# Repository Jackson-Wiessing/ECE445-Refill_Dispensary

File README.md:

# ECE445-Refill_Dispensary

**Welcome to our refill dispensary repo!**

**Introduction:** 

Plastic waste is a massive issue world-wide, particularly as it pertains to the packaging of food and other household goods. The United States Environmental Protection Agency estimates that in 2018, 14 million tons of plastic was consumed for packaging in the USA with about seventy percent of that ending up in landfills[1]. Plastic waste is detrimental to the environment as it doesn’t decompose naturally on human time scales. End-user plastic waste is often unnecessary as consumers own containers capable of being reused. 

We built a vending machine that dispenses precise quantities of goods (between 10 g and 5 kg) into reusable containers. The goal of the machine is to get users to keep bringing the same container back. In addition to plastic waste, our machine tackles the issue of waste in general as users are no longer forced to get quantities larger than desired. 

**High-level requirements:**
1. The user is able to choose an item and quantity to get dispensed via buttons and rotary potentiometers. Before placing the order, the user will have some indication of the amount ordered within a tolerance of 10 grams for weights between .1 kg and 2kg.
2. The machine dispenses two different types of low-viscosity liquids and is able to perform 2 orders in succession. 
3. The machine can deliver another order properly after 1 of the liquids is switched out or refilled. 

**Block Diagram:**

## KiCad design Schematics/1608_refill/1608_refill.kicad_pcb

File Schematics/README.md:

The easiest way to view our schematic and PCB layout is to download KiCad from https://www.kicad.org/download/. 
Once KiCad is downloaded, you'll need to clone this repo on your local machine.

To see the schematic open 1608_refill.kicad_sch.   

To see the PCB layout open 1608_refill.kicad_pcb.

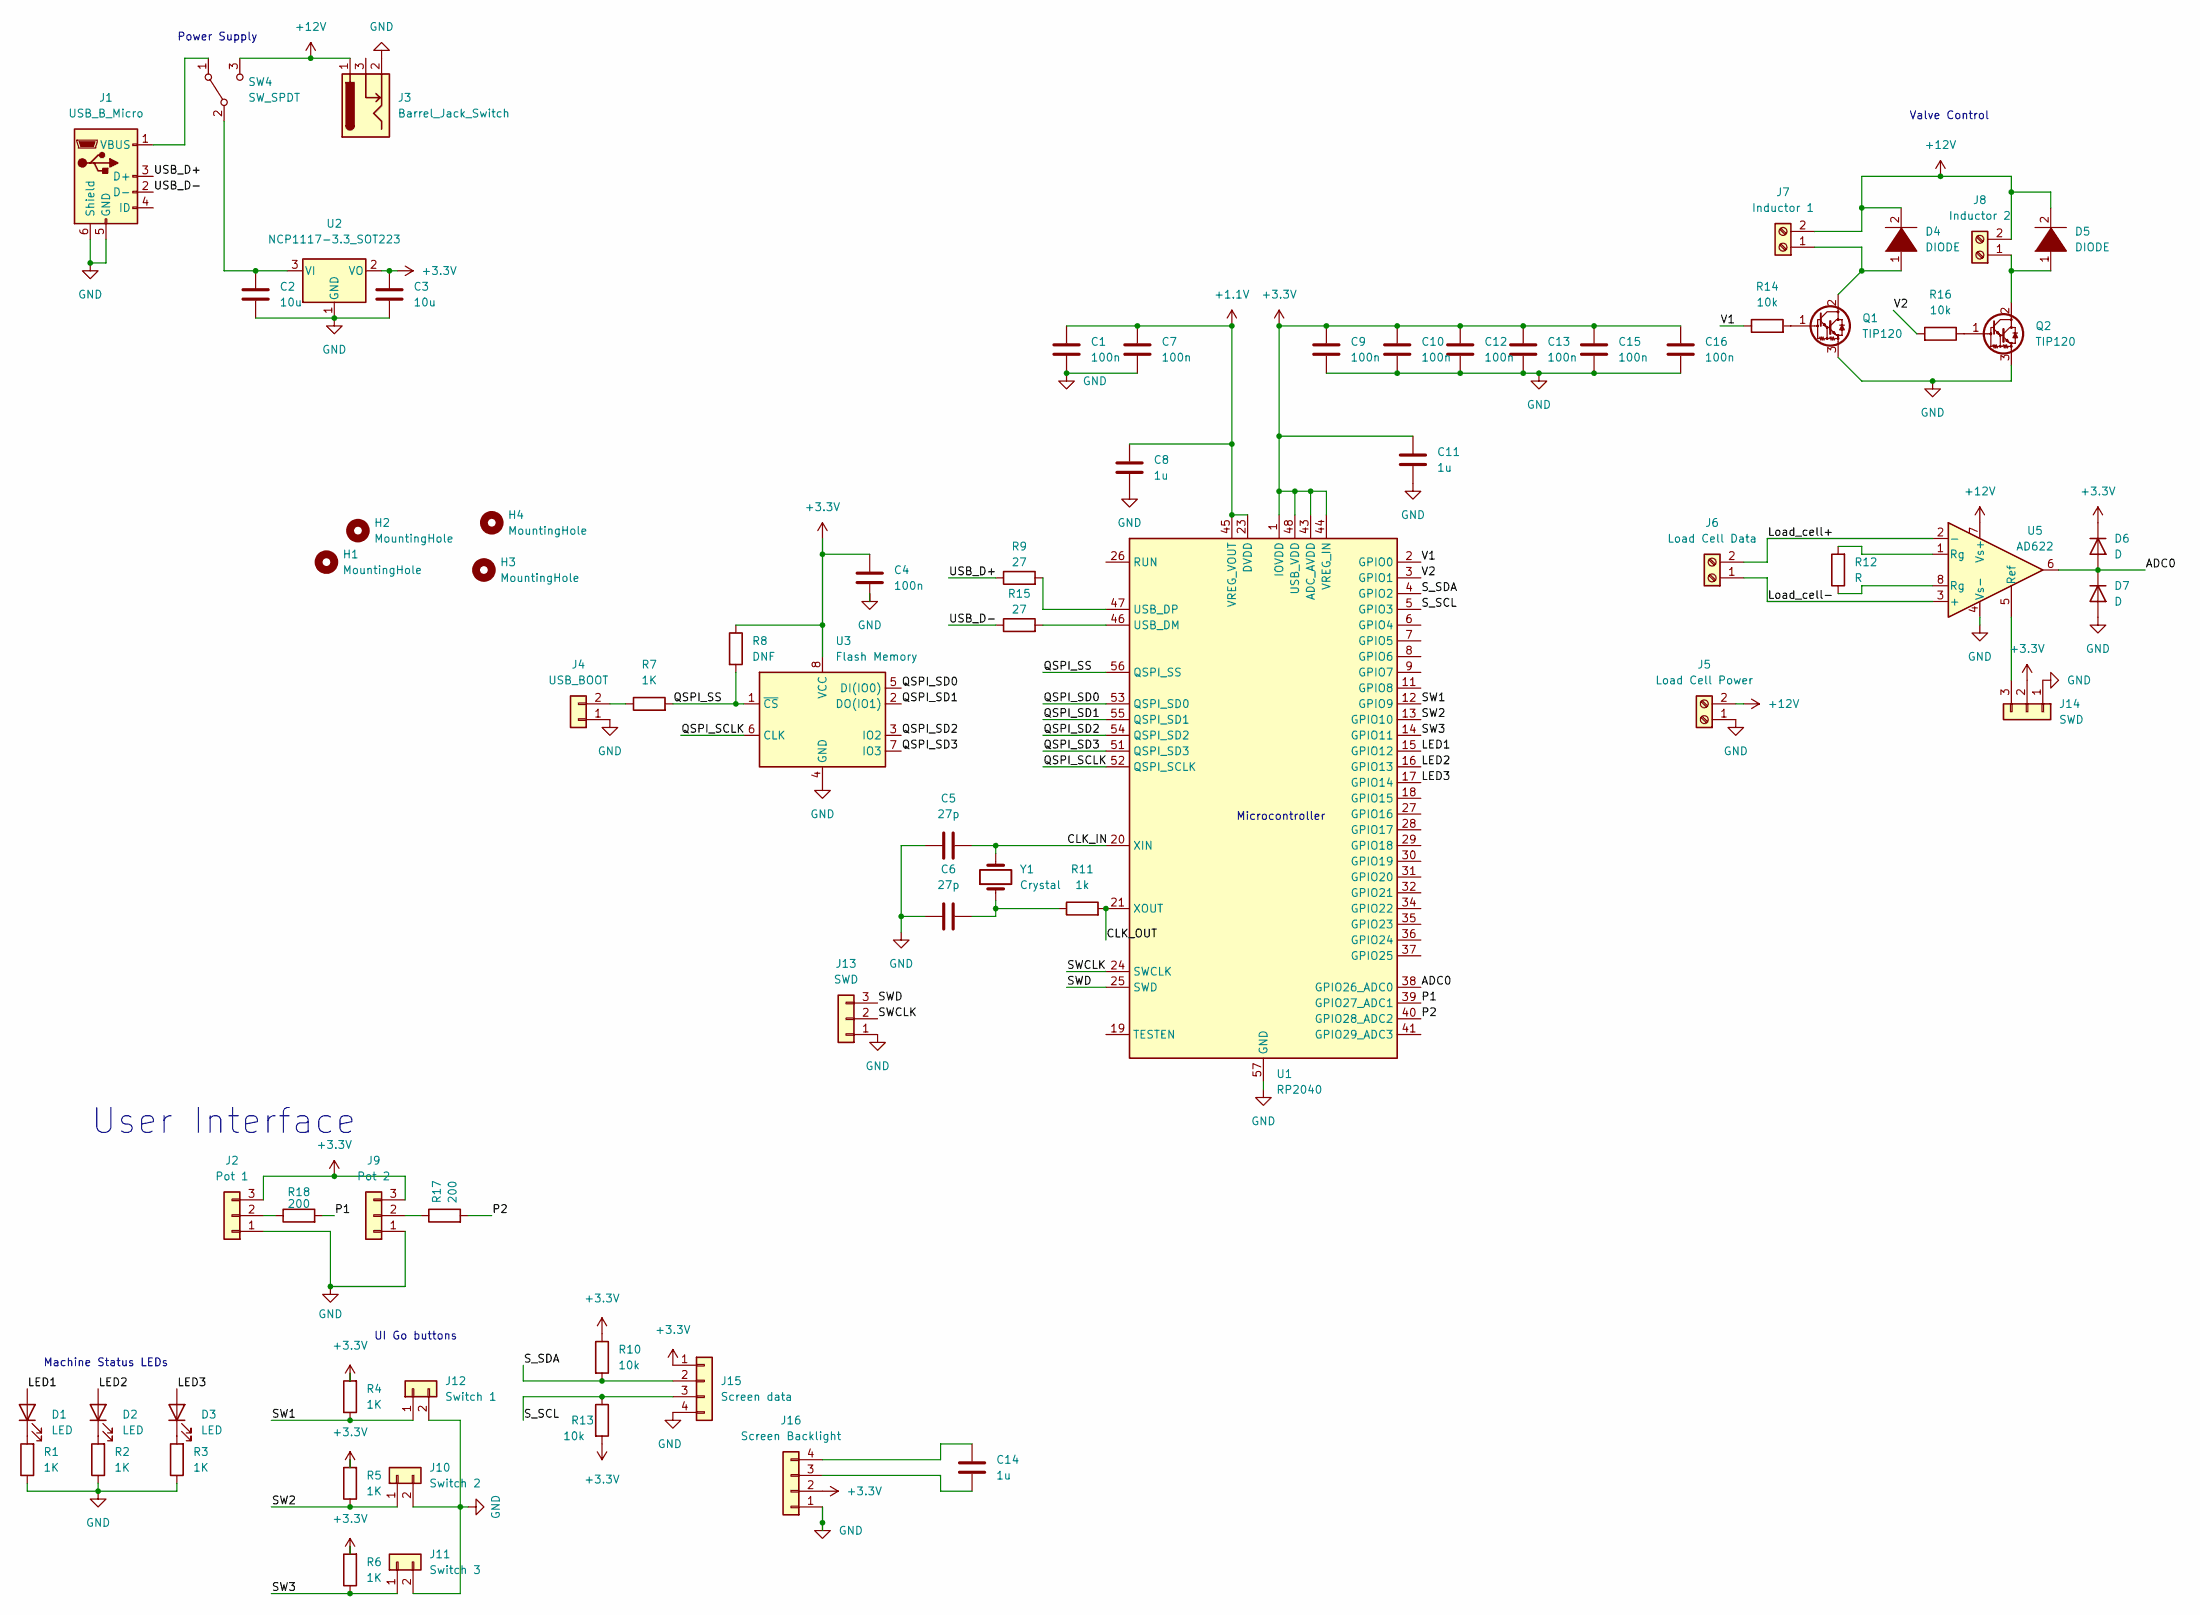
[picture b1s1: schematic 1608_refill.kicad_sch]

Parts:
C1, C4, C7, C9, C10, C12, C13, C15, C16: 100n; C_0603_1608Metric_Pad1.08x0.95mm_HandSolder
C2, C3: 10u; C_1210_3225Metric
C5, C6: 27p; C_0805_2012Metric
C8, C11, C14: 1u; C_0603_1608Metric_Pad1.08x0.95mm_HandSolder
D1, D2, D3: LED; LED_D3.0mm
D4, D5: DIODE; D_5W_P5.08mm_Vertical_AnodeUp
D6, D7: D; D_5W_P5.08mm_Vertical_AnodeUp
H1, H2, H3, H4: MountingHole; MountingHole_2.1mm
J1: USB_B_Micro; USB_Micro-AB_Molex_47590-0001
J2: Pot 1; JST_XH_B3B-XH-AM_1x03_P2.50mm_Vertical
J3: Barrel_Jack_Switch; BarrelJack_GCT_DCJ200-10-A_Horizontal
J4: USB_BOOT; JWT_A3963_1x02_P3.96mm_Vertical
J5: Load Cell Power; TerminalBlock_Altech_AK300-2_P5.00mm
J6: Load Cell Data; TerminalBlock_Altech_AK300-2_P5.00mm
J7: Inductor 1; TerminalBlock_Altech_AK300-2_P5.00mm
J8: Inductor 2; TerminalBlock_Altech_AK300-2_P5.00mm
J9: Pot 2; JST_XH_B3B-XH-AM_1x03_P2.50mm_Vertical
J10: Switch 2; JST_XH_B2B-XH-AM_1x02_P2.50mm_Vertical
J11: Switch 3; JST_XH_B2B-XH-AM_1x02_P2.50mm_Vertical
J12: Switch 1; JST_XH_B2B-XH-AM_1x02_P2.50mm_Vertical
J13, J14: SWD; JST_XH_B3B-XH-AM_1x03_P2.50mm_Vertical
J15: Screen data; JST_XH_B4B-XH-AM_1x04_P2.50mm_Vertical
J16: Screen Backlight; JST_XH_B4B-XH-AM_1x04_P2.50mm_Vertical
Q1, Q2: TIP120; TO-220-3_Vertical
R1, R2, R3, R4, R5, R6, R7: 1K; R_0603_1608Metric_Pad0.98x0.95mm_HandSolder
R8: DNF; R_0603_1608Metric_Pad0.98x0.95mm_HandSolder
R9, R15: 27; R_0805_2012Metric
R10, R13, R14, R16: 10k; R_0603_1608Metric_Pad0.98x0.95mm_HandSolder
R11: 1k; R_0603_1608Metric_Pad0.98x0.95mm_HandSolder
R12: R; R_Axial_DIN0204_L3.6mm_D1.6mm_P7.62mm_Horizontal
R17, R18: 200; R_0603_1608Metric_Pad0.98x0.95mm_HandSolder
SW4: SW_SPDT; SW_SPDT_CK-JS102011SAQN
U1: RP2040; QFN-56-1EP_7x7mm_P0.4mm_EP3.2x3.2mm
U2: NCP1117-3.3_SOT223; SOT-223-3_TabPin2
U3: Flash Memory; SOIC-8_5.23x5.23mm_P1.27mm
U5: AD622
Y1: Crystal; ABLS12MHZ

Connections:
+1V1: C1.1, C7.1, C8.1, U1.23 (DVDD), U1.45 (VREG_VOUT), U1.50 (DVDD)
+3.3V: C3.1, C4.1, C9.1, C10.1, C11.1, C12.1, C13.1, C15.1, C16.1, D6.1 (K), J2.3, J9.3, J14.2, J15.1, J16.2, R4.2, R5.2, R6.2, R8.1, R10.1, R13.2, U1.1 (IOVDD), U1.10 (IOVDD), U1.22 (IOVDD), U1.33 (IOVDD), U1.42 (IOVDD), U1.43 (ADC_AVDD), U1.44 (VREG_IN), U1.48 (USB_VDD), U1.49 (IOVDD), U2.2 (VO), U3.8 (VCC)
+12V: D4.2 (A), D5.2 (A), J3.1, J5.2, J7.2, J8.2, SW4.3 (C), U5.7 (Vs+)
/ADC0: D6.2 (A), D7.1 (K), U1.38 (GPIO26_ADC0), U5.6
/CLK_IN: C5.2, U1.20 (XIN), Y1.2
/CLK_OUT: R11.2, U1.21 (XOUT)
/LED1: D1.2 (A), U1.15 (GPIO12)
/LED2: D2.2 (A), U1.16 (GPIO13)
/LED3: D3.2 (A), U1.17 (GPIO14)
/Load_cell+: J6.2, U5.2 (-)
/Load_cell-: J6.1, U5.3 (+)
/P1: R18.2, U1.39 (GPIO27_ADC1)
/P2: R17.2, U1.40 (GPIO28_ADC2)
/QSPI_SCLK: U1.52 (QSPI_SCLK), U3.6 (CLK)
/QSPI_SD0: U1.53 (QSPI_SD0), U3.5 (DI(IO0))
/QSPI_SD1: U1.55 (QSPI_SD1), U3.2 (DO(IO1))
/QSPI_SD2: U1.54 (QSPI_SD2), U3.3 (IO2)
/QSPI_SD3: U1.51 (QSPI_SD3), U3.7 (IO3)
/QSPI_SS: R7.2, R8.2, U1.56 (QSPI_SS), U3.1 (~CS)
/SW1: J12.1, R4.1, U1.12 (GPIO9)
/SW2: J10.1, R5.1, U1.13 (GPIO10)
/SW3: J11.1, R6.1, U1.14 (GPIO11)
/SWCLK: J13.2, U1.24 (SWCLK)
/SWD: J13.3, U1.25 (SWD)
/S_SCL: J15.3, R13.1, U1.5 (GPIO3)
/S_SDA: J15.2, R10.2, U1.4 (GPIO2)
/USB_D+: J1.3 (D+), R9.1
/USB_D-: J1.2 (D-), R15.1
/V1: R14.1, U1.2 (GPIO0)
/V2: R16.2, U1.3 (GPIO1)
GND: C1.2, C2.2, C3.2, C4.2, C5.1, C6.1, C7.2, C8.2, C9.2, C10.2, C11.2, C12.2, C13.2, C15.2, C16.2, D7.2 (A), J1.5 (GND), J1.6 (Shield), J2.1, J3.2, J4.1, J5.1, J9.1, J10.2, J11.2, J12.2, J13.1, J14.1, J15.4, J16.1, Q1.3 (E), Q2.3 (E), R1.1, R2.1, R3.1, U1.57 (GND), U2.1 (GND), U3.4 (GND), U5.4 (Vs-)
unnamed: C2.1, SW4.2 (B), U2.3 (VI)
unnamed: C6.2, R11.1, Y1.1
unnamed: C14.1, J16.4
unnamed: C14.2, J16.3
unnamed: D1.1 (K), R1.2
unnamed: D2.1 (K), R2.2
unnamed: D3.1 (K), R3.2
unnamed: D4.1 (K), J7.1, Q1.2 (C)
unnamed: D5.1 (K), J8.1, Q2.2 (C)
unnamed: J1.1 (VBUS), SW4.1 (A)
unnamed: J2.2, R18.1
unnamed: J4.2, R7.1
unnamed: J9.2, R17.1
unnamed: J14.3, U5.5 (Ref)
unnamed: Q1.1 (B), R14.2
unnamed: Q2.1 (B), R16.1
unnamed: R9.2, U1.47 (USB_DP)
unnamed: R12.1, U5.8 (Rg)
unnamed: R12.2, U5.1 (Rg)
unnamed: R15.2, U1.46 (USB_DM)

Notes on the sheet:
Machine Status LEDs
Microcontroller
Power Supply
Valve Control
User Interface
UI Go buttons

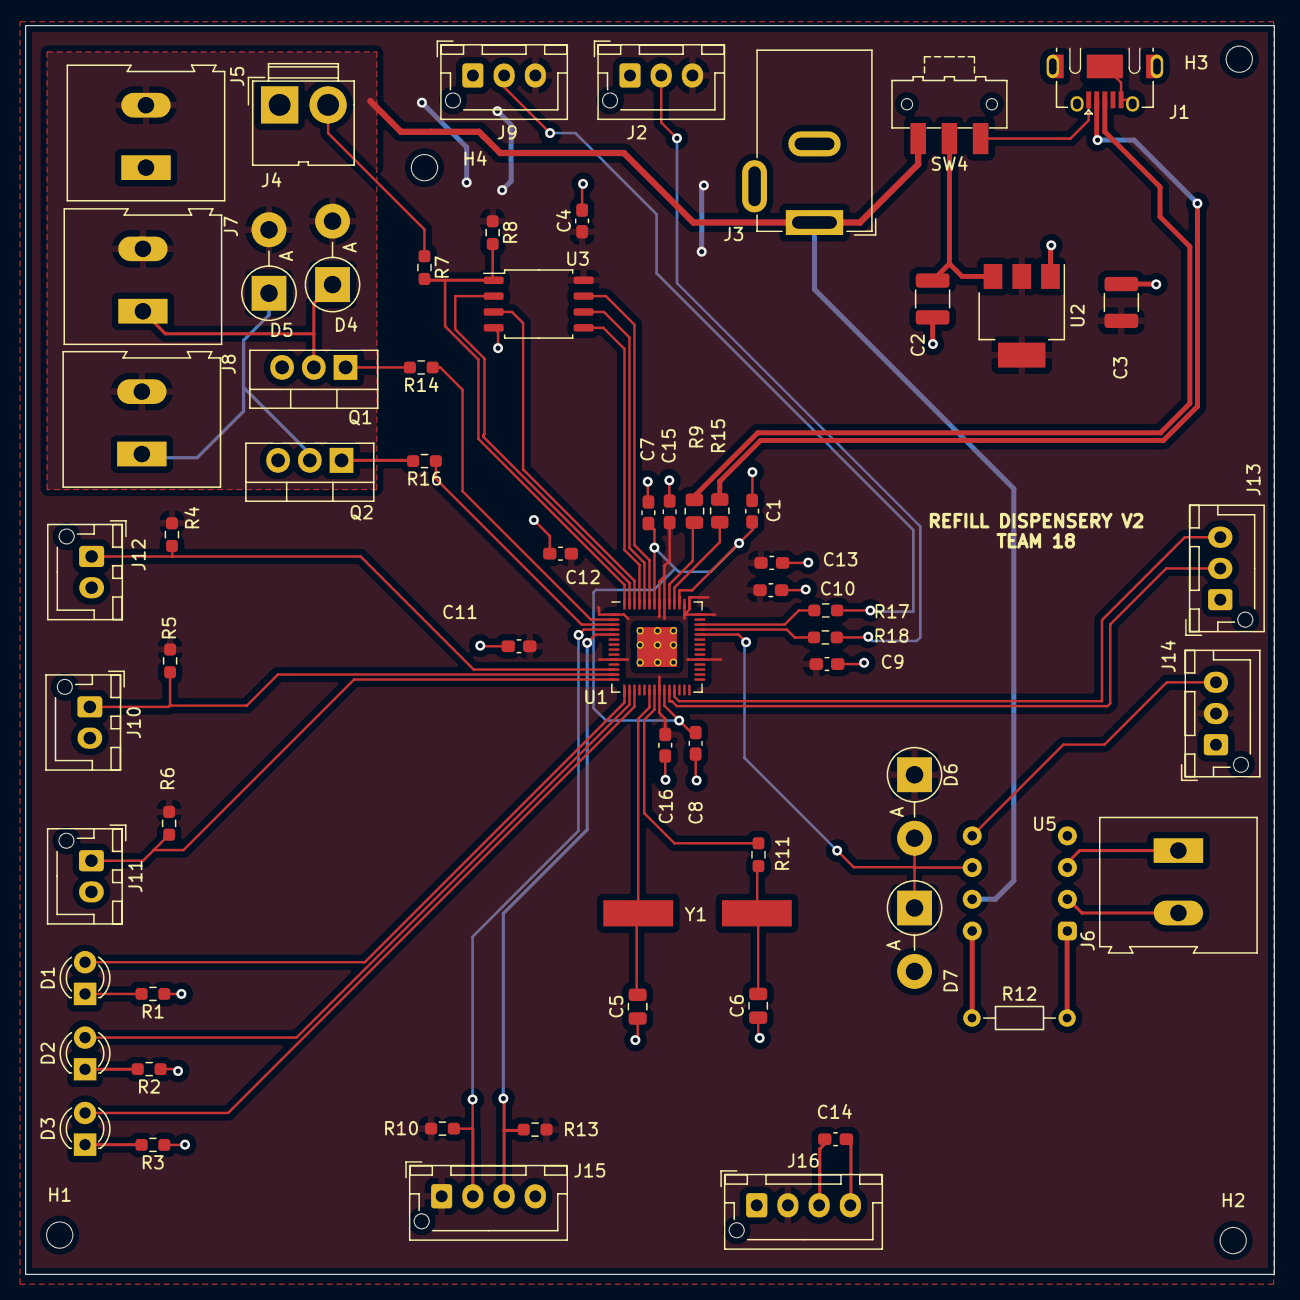
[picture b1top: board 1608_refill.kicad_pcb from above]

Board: 2 copper layers, 100.0 x 100.0 mm, 69 parts (0 on the bottom side), 51 nets.

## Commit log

2022-09-19 Initial Schematic Drawing
2022-09-19 Schematic Outline
2022-09-21 some updates
2022-09-24 Schematic mostly done
2022-09-26 minor changes
2022-10-08 hello
2022-10-08 organizing
2022-10-08 everything is pretty
2022-10-09 I'm cant make a PCB
2022-10-10 I'm cant make a PCB again
2022-10-10 board mostly finished
2022-10-10 update screen schematic
2022-10-11 board v1
2022-10-11 board v1.1
2022-10-18 starting the software
2022-10-18 writing unit tests
2022-10-18 will do more after parts are acquired, Michael is doing pseudocode rn
2022-10-22 main arduino code added
2022-10-22 typo changed in code
2022-10-22 better quality pic
2022-10-30 early 1608 upgrade sketches
2022-10-30 cleanup
2022-10-30 progress
2022-10-30 gearing up for PCB 2
2022-10-31 more updates
2022-10-31 will do more tomorrow
2022-11-01 hurry up amazon with those new Picos
2022-11-01 screen code coming soon
2022-11-03 GPIO # NOT PINS!!!!
2022-11-05 1608:all routes connected
2022-11-06 1608 mostly done
2022-11-16 Works with the new screen
2022-11-16 load cell with the HX711 chip -> reads values
2022-11-16 takes awhile but gets a semi-stable reading
2022-11-17 The load cell works within the tolerance!
2022-11-18 main loop micropython added
2022-11-18 Load Cell is being bad today
2022-11-18 changed screen code to micropython
2022-11-18 Made code readable
2022-11-26 fixed pico main loop, now uses gpio pin initialization
2022-11-26 added bottle status text file
2022-11-27 fixed formatting
2022-11-30 crap
